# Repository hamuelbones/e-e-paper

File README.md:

# ESP-32 battery-powered ePaper Display

This repository hosts hardware and firmware files for an e-paper display board!

[Documentation is being hosted here!](https://hamuelbones.github.io/e-e-paper/)

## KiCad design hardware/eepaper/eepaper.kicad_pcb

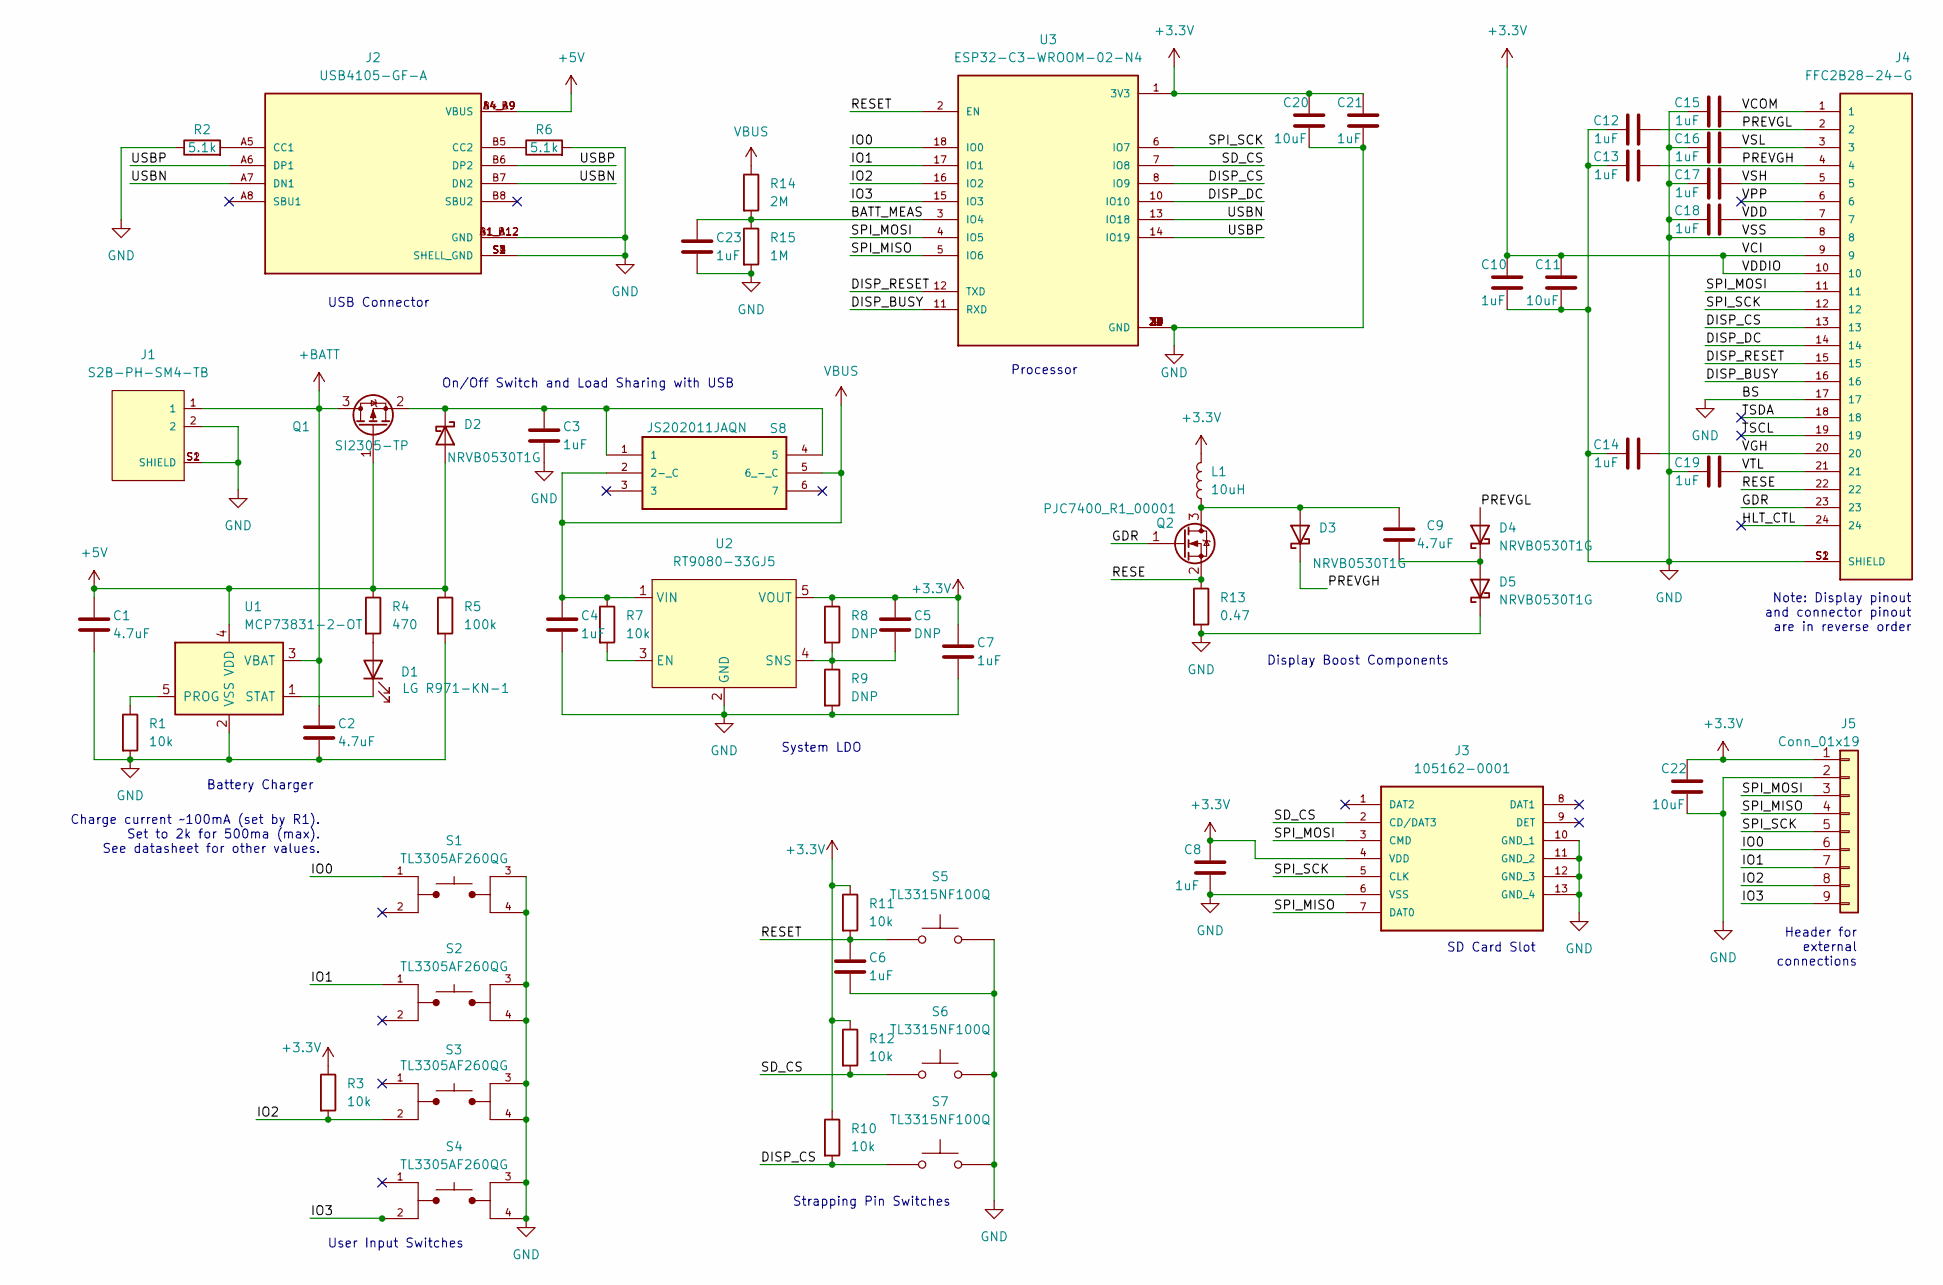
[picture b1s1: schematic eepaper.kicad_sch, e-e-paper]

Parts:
C1, C2, C9: 4.7uF; C_0805_2012Metric_Pad1.18x1.45mm_HandSolder
C3, C4, C6, C7, C8, C10, C12, C13, C14, C15, C16, C17, C18, C19, C21, C23: 1uF; C_0805_2012Metric_Pad1.18x1.45mm_HandSolder
C5: DNP; C_0805_2012Metric_Pad1.18x1.45mm_HandSolder
C11, C20, C22: 10uF; C_0805_2012Metric_Pad1.18x1.45mm_HandSolder
D1: LG R971-KN-1; LED_0805_2012Metric_Pad1.15x1.40mm_HandSolder
D2, D3, D4, D5: NRVB0530T1G; D_SOD-123
J1: S2B-PH-SM4-TB; JST_S2B-PH-SM4-TB(LF)(SN)
J2: USB4105-GF-A; GCT_USB4105-GF-A; PARTREV A3
J3: 105162-0001; MANUFACTURER_PART_NUMBER 105162-0001; MOUSER_PART_NUMBER 538-105162-0001
J4: FFC2B28-24-G; GCT_FFC2B28-24-G; PARTREV A
J5: Conn_01x19; PinHeader_1x09_P2.54mm_Horizontal
L1: 10uH; L_0805_2012Metric_Pad1.15x1.40mm_HandSolder
Q1: SI2305-TP; SOT-23
Q2: PJC7400_R1_00001; SOT-323_SC-70_Handsoldering
R1, R3, R7, R10, R11, R12: 10k; R_0805_2012Metric_Pad1.20x1.40mm_HandSolder
R2, R6: 5.1k; R_0805_2012Metric_Pad1.20x1.40mm_HandSolder
R4: 470; R_0805_2012Metric_Pad1.20x1.40mm_HandSolder
R5: 100k; R_0805_2012Metric_Pad1.20x1.40mm_HandSolder
R8, R9: DNP; R_0805_2012Metric_Pad1.20x1.40mm_HandSolder
R13: 0.47; R_0805_2012Metric_Pad1.20x1.40mm_HandSolder
R14: 2M; R_0805_2012Metric_Pad1.20x1.40mm_HandSolder
R15: 1M; R_0805_2012Metric_Pad1.20x1.40mm_HandSolder
S1, S2, S3, S4: TL3305AF260QG; SW_TL3305AF260QG; PARTREV C
S5, S6, S7: TL3315NF100Q; SW_TL3315NF100Q
S8: JS202011JAQN; MANUFACTURER_PART_NUMBER JS202011JAQN
U1: MCP73831-2-OT; SOT-23-5
U2: RT9080-33GJ5; SOT-23-5_HandSoldering
U3: ESP32-C3-WROOM-02-N4; MODULE_ESP32-C3-WROOM-02-H4; PARTREV V1.0

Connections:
+3V3: C5.1, C7.1, C8.1, C10.1, C11.1, C20.1, C21.1, C22.1, J3.4 (VDD), J4.9, J4.10, J5.1, L1.2, R3.1, R8.1, R10.1, R11.1, R12.1, U2.5 (VOUT), U3.1 (3V3)
+5V: C1.1, D2.2 (A), J2.A4_B9 (VBUS), J2.B4_A9 (VBUS), Q1.1 (G), R4.1, R5.1, U1.4 (VDD)
+BATT: C2.1, J1.1, Q1.3 (D), U1.3 (VBAT)
/BATT_MEAS: C23.1, R14.2, R15.1, U3.3 (IO4)
/DISP_BUSY: J4.16, U3.11 (RXD)
/DISP_CS: J4.13, R10.2, S7.1, S7.2, U3.8 (IO9)
/DISP_DC: J4.14, U3.10 (IO10)
/DISP_RESET: J4.15, U3.12 (TXD)
/GDR: J4.23, Q2.1 (G)
/HLT_CTL: J4.24
/IO0: J5.6, S1.1, U3.18 (IO0)
/IO1: J5.7, S2.1, U3.17 (IO1)
/IO2: J5.8, R3.2, S3.2, U3.16 (IO2)
/IO3: J5.9, S4.2, U3.15 (IO3)
/PREVGH: C13.2, D3.1 (K), J4.4
/PREVGL: C12.2, D4.2 (A), J4.2
/RESE: J4.22, Q2.2 (S), R13.1
/RESET: C6.1, R11.2, S5.1, S5.2, U3.2 (EN)
/SD_CS: J3.2 (CD/DAT3), R12.2, S6.1, S6.2, U3.7 (IO8)
/SPI_MISO: J3.7 (DAT0), J5.4, U3.5 (IO6)
/SPI_MOSI: J3.3 (CMD), J4.11, J5.3, U3.4 (IO5)
/SPI_SCK: J3.5 (CLK), J4.12, J5.5, U3.6 (IO7)
/TSCL: J4.19
/TSDA: J4.18
/USBN: J2.A7 (DN1), J2.B7 (DN2), U3.13 (IO18)
/USBP: J2.A6 (DP1), J2.B6 (DP2), U3.14 (IO19)
/VCOM: C15.2, J4.1
/VDD: C18.2, J4.7
/VGH: C14.2, J4.20
/VPP: J4.6
/VSH: C17.2, J4.5
/VSL: C16.2, J4.3
/VTL: C19.2, J4.21
GND: C1.2, C2.2, C3.2, C4.2, C6.2, C7.2, C8.2, C10.2, C11.2, C12.1, C13.1, C14.1, C15.1, C16.1, C17.1, C18.1, C19.1, C20.2, C21.2, C22.2, C23.2, D5.1 (K), J1.2, J1.S1 (SHIELD), J1.S2 (SHIELD), J2.A1_B12 (GND), J2.B1_A12 (GND), J2.S1 (SHELL_GND), J2.S2 (SHELL_GND), J2.S3 (SHELL_GND), J2.S4 (SHELL_GND), J3.6 (VSS), J3.10 (GND_1), J3.11 (GND_2), J3.12 (GND_3), J3.13 (GND_4), J4.8, J4.17, J4.S1 (SHIELD), J4.S2 (SHIELD), J5.2, R1.2, R2.1, R5.2, R6.2, R9.2, R13.2, R15.2, S1.3, S1.4, S2.3, S2.4, S3.3, S3.4, S4.3, S4.4, S5.3, S5.4, S6.3, S6.4, S7.3, S7.4, U1.2 (VSS), U2.2 (GND), U3.9 (GND), U3.19 (GND), U3.20 (GND), U3.21 (GND), U3.22 (GND), U3.23 (GND), U3.24 (GND), U3.25 (GND), U3.26 (GND), U3.27 (GND), U3.28 (GND), U3.29 (GND), U3.30 (GND), U3.31 (GND), U3.32 (GND), U3.33 (GND), U3.34 (GND), U3.35 (GND), U3.36 (GND), U3.37 (GND), U3.38 (GND), U3.39 (GND)
unnamed: C3.1, D2.1 (K), Q1.2 (S), S8.1, S8.4 (5)
unnamed: C5.2, R8.2, R9.1, U2.4 (SNS)
unnamed: C9.1, D4.1 (K), D5.2 (A)
unnamed: C9.2, D3.2 (A), L1.1, Q2.3 (D)
unnamed: D1.1 (K), U1.1 (STAT)
unnamed: D1.2 (A), R4.2
unnamed: J2.A5 (CC1), R2.2
unnamed: J2.B5 (CC2), R6.1
unnamed: R1.1, U1.5 (PROG)
unnamed: R7.2, U2.3 (EN)
VBUS: C4.1, R7.1, R14.1, S8.2 (2-_C), S8.5 (6_-_C), U2.1 (VIN)

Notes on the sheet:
System LDO
User Input Switches
Display Boost Components
Processor
Note: Display pinout and connector pinout are in reverse order
Charge current ~100mA (set by R1). Set to 2k for 500ma (max). See datasheet for other values.
Strapping Pin Switches
USB Connector
Battery Charger
On/Off Switch and Load Sharing with USB
SD Card Slot
Header for external connections

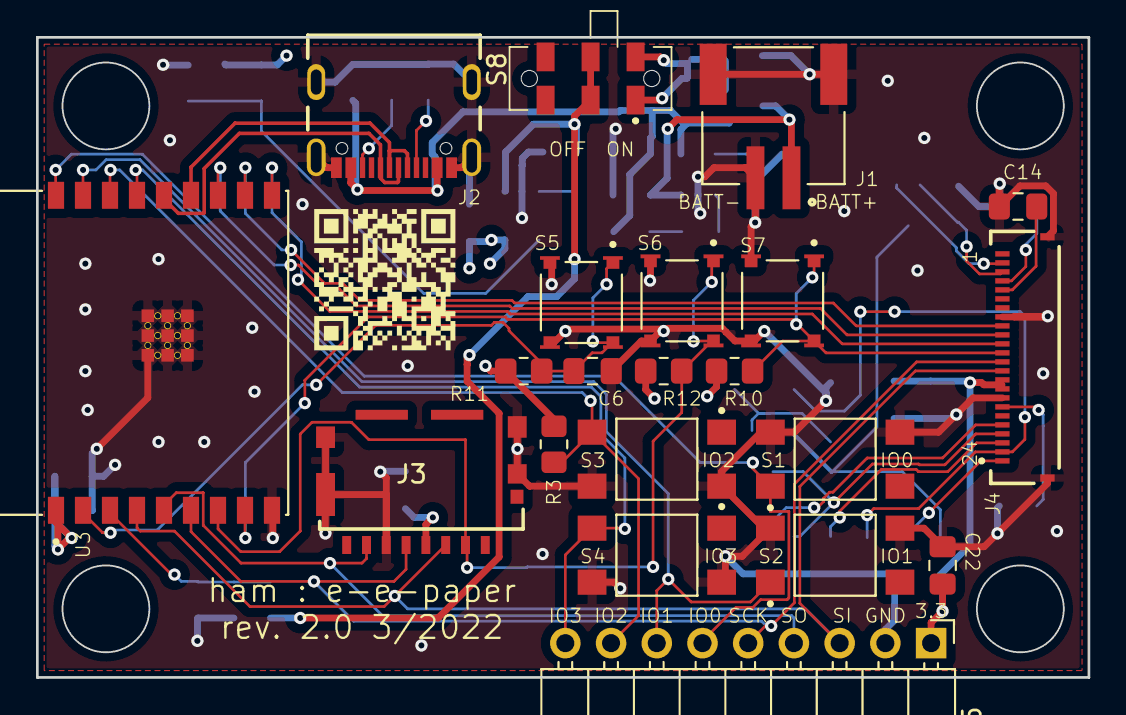
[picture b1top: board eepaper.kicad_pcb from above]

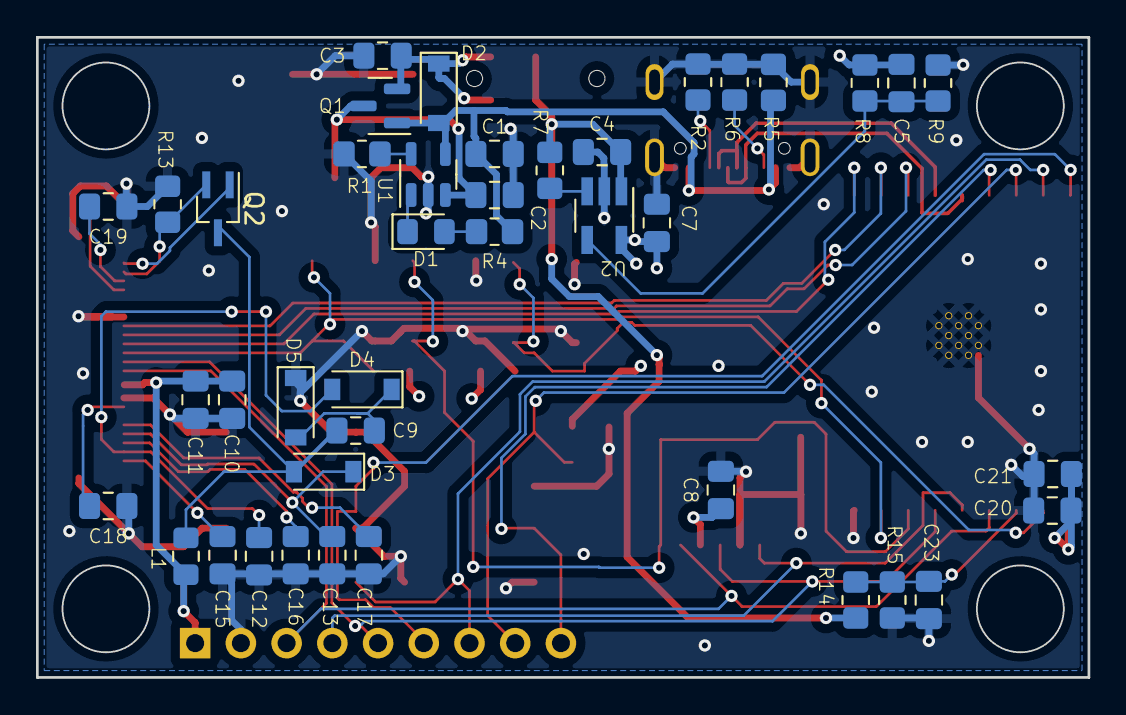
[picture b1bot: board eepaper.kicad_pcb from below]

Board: 4 copper layers, 58.4 x 35.6 mm, 62 parts (41 on the bottom side), 41 nets.

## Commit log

2021-12-01 working: wifi connection, display test pattern/refresh
2021-12-10 demo of 7x5 display
2021-12-19 Display buffer update.
2021-12-20 Font rendering demo works!
2021-12-24 Get display buffer swapping back in
2021-12-26 Change pins for HW v1 board
2021-12-26 Update SDK config for v1 board
2021-12-26 Add default charger pin configs
2021-12-26 Fix usb breaking on wifi start by sdk config
2021-12-28 Move source around and get used to weird idf component cmake extensions
2021-12-31 Add simulator target! Some restructuring of overall code and display code.
2022-01-01 Add a working multiline string rendering function!
    Needs a bit more work but most common scenarios seem to be good
2022-01-01 Add template files
2022-01-02 Start using free fonts. Automatic bitmap conversion of ebook fonts doesn't look that great at low res though, may need some tailored bitfonts from somewhere.
2022-01-07 Add vertical text justification flags, if hacky
2022-01-07 Some manual font fixing.
2022-01-09 Major changes - overall app structure, loading from file, and toml parser all working in simulator. Not working on device yet.
2022-01-10 WIP update
2022-01-11 WIP playing around with OpenSSL integration
2022-01-13 fonts: start cleaning up the 48 pt
2022-01-18 Implement symbol rendering and start adding system symbols.
2022-01-18 E-paper app: minor cleanup
2022-01-18 Be able to draw symbols with justification flags
2022-01-19 Get on-hardware target setup working again
2022-01-20 SD card filesystem demo working on HW!
2022-01-21 Testing basic simulator crypto functions
2022-01-21 JWT generation working in simulator!
2022-01-22 Getting network requests working in the simulator!
2022-01-22 Demo authorization to local dev server with a JWT and RSA! :)
2022-01-22 Simulator: get network time
2022-01-25 Everything's broken while hooking things together
2022-01-26 Starting simulator integration of online mode
2022-01-28 Fetching configuration and generic resources from a server now works in simulation!
2022-01-28 Add some SPIFFS setup. untested
2022-01-29 Get target build working with stubs
2022-01-30 Initial untested HAL implementations to catch HAL up with simulator
2022-01-31 WIP getting hardware target functional again
2022-01-31 Current version now works on hardware :)
2022-02-01 We're now substituting in messages!!
2022-02-01 Add script to convert images into a YAFF file
2022-02-01 Script to convert a yaff to a binary file.
2022-02-02 Can load external fonts!
2022-02-02 Add and use new fonts - New York from hoard of bitfonts repository
2022-02-02 MVP for device wedding message display working :) Added rectangle rendering and custom symbols
2022-02-03 Remove default wifi password :P
2022-02-04 add some (hopeful) logic to unstick the device from common stuck cases
2022-02-04 Update power management settings - first pass
2022-02-15 Make naming scheme consistent - old habits die hard
2022-02-16 Fix warnings.
2022-02-16 Fix one more warning
2022-02-17 A bit of file cleanup and refactoring
2022-02-17 Fix build error
2022-02-17 Set theme jekyll-theme-minimal
2022-02-17 Add boilerplate github pages site
2022-02-17 More github pages setup
2022-02-18 More docs setup
2022-02-18 Refactor function names for consistency and allow for runtime simulator filesystem paths
2022-02-19 Update user guide
2022-02-23 Add time hal and clock app, though this may not end up existing like an "app" does.
2022-02-23 Some openSSL fixes
2022-02-24 Commiting doc theme updates, not sure if this works yet
2022-02-24 Refactor resource code structure in preparation for greater rendering refactor
2022-02-24 Fix target build and move resource files to their own directory
2022-02-25 In the middle of refactoring rendering code and methodology
2022-02-25 Fixes for rendering core and add general line drawing :)
2022-02-26 Add symbol and text drawing, fix a bunch of bugs
2022-02-26 Now, we can do string substitutions from references in the config.toml.
2022-02-27 The combined app mode is working!
2022-02-27 Clock resource added! Now the time can be referenced in display configs.
2022-03-01 Remove old rendering code and get working on hardware (rendering, at least)
2022-03-01 Integrate SSL option into simulator and hardware
2022-03-01 Fix some memory leaks from toml string gets that I didn't realize needed to be freed.
2022-03-02 OTA update checks... something is not quite right though
2022-03-02 ota update support changes
2022-03-02 Undo this change
2022-03-02 fixed my silly string bug
2022-03-02 more memory leak fixes... now, at least memory usage looks stable when idly running and refreshing.
2022-03-02 add fab files for v1
2022-03-03 Starting to test OTA update - not working yet
2022-03-09 Add v2 hardware files
2022-03-10 Add v2 hardware files sent to fabrication
2022-03-12 Inching toward multiple display support
2022-03-12 Continue to work to multi-display
2022-03-12 Getting closer to multi-display support!
2022-03-12 Fix DC pin not being set correctly when writing data
2022-03-13 Multi-display types working on hardware and in simulator (bw full-refresh only so far)
2022-03-22 Add v2 pinouts and build flag.
2022-03-27 Hacking just in time for a niece's birthday present. Will need to parameterize a bunch of this later
2022-04-19 Don't use external theme
2022-11-06 Update esp-idf to 5.0 release version and fix warnings/errors.
